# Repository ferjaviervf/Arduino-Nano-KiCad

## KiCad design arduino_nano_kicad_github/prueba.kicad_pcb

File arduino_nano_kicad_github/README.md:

# Placa basada en ATmega328 (KiCad)

Proyecto de diseño electrónico en KiCad, con esquema y circuito impreso de una placa basada en el microcontrolador **ATmega328-M**.

## Archivos

- `prueba.kicad_pro` — configuración del proyecto.
- `prueba.kicad_sch` — esquema electrónico.
- `prueba.kicad_pcb` — diseño de la placa PCB.

## Cómo abrirlo

1. Descarga o clona este repositorio.
2. Abre `prueba.kicad_pro` con KiCad.
3. Usa el editor de esquemas o PCB para revisar y modificar el diseño.

> **Estado:** Proyecto de diseño. No se han verificado aquí la compatibilidad total con Arduino Nano, las reglas eléctricas (ERC), las reglas de diseño (DRC) ni el funcionamiento de una placa fabricada.

## Publicación

Esta es la primera versión de mi placa basada en Arduino Nano. Estoy aprendiendo a usar KiCad, así que es probable que tenga algunos errores. Agradecería mucho cualquier comentario o retroalimentación para mejorarla.

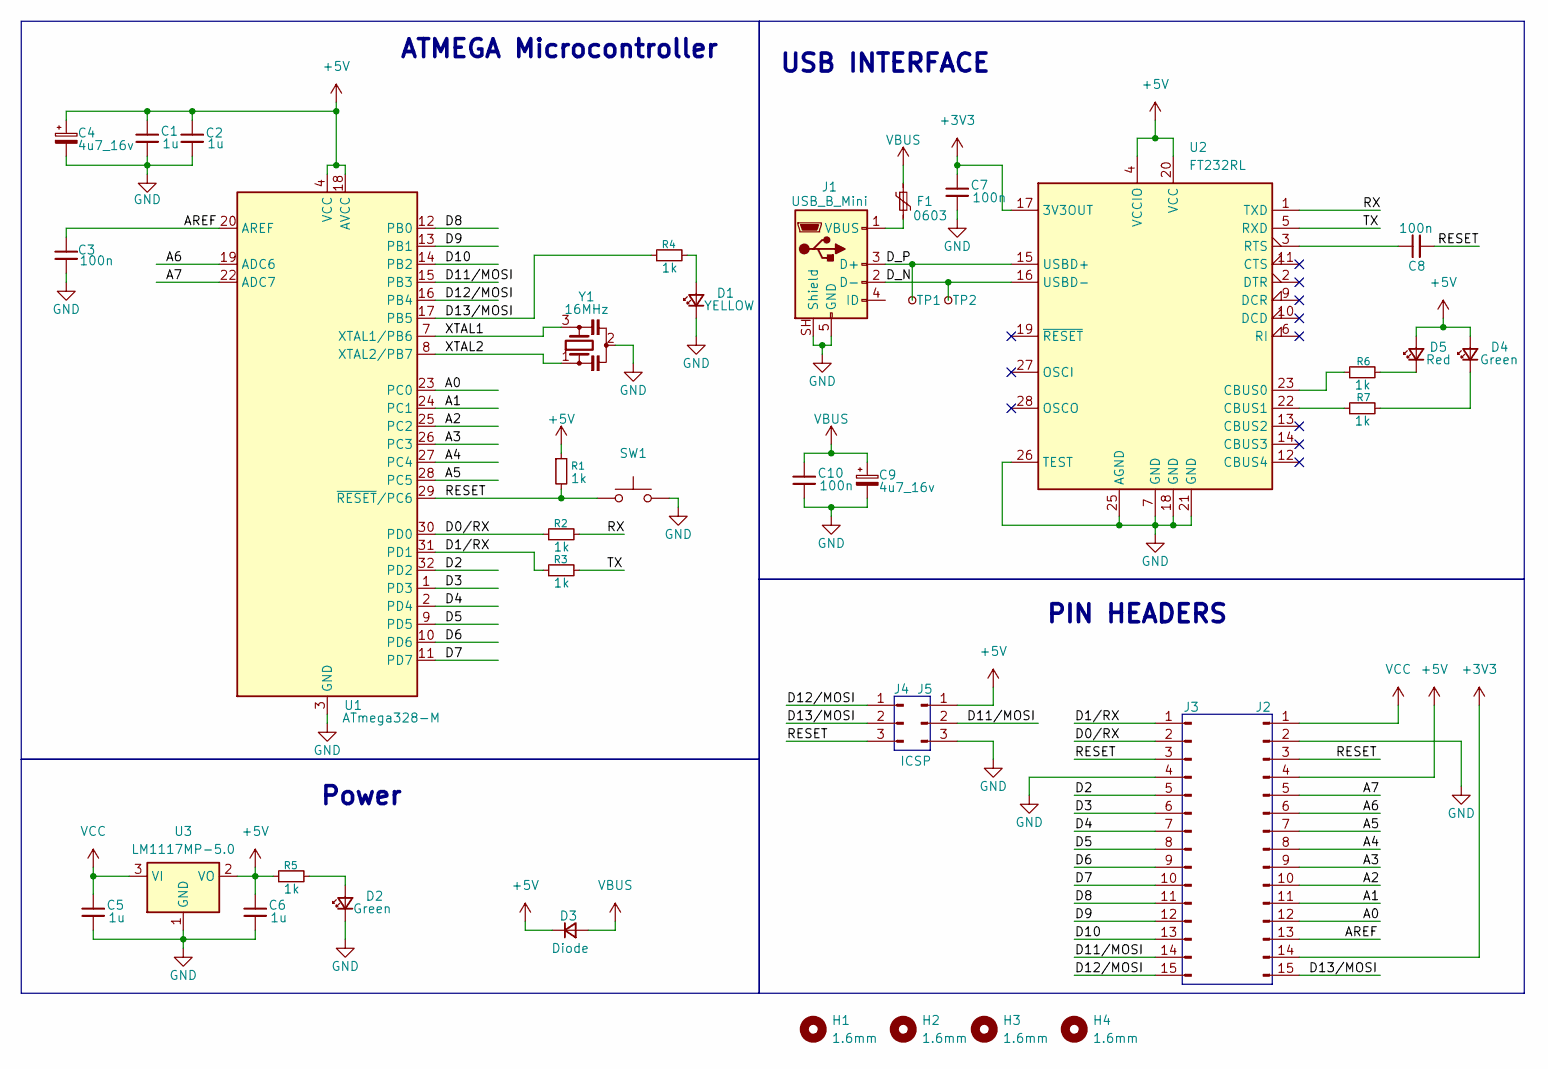
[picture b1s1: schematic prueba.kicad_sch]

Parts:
C1, C2, C5, C6: 1u; C_0603_1608Metric
C3, C7, C8, C10: 100n; C_0603_1608Metric
C4, C9: 4u7_16v; CP_EIA-3216-10_Kemet-I
D1: YELLOW; LED_0805_2012Metric
D2, D4: Green; LED_0805_2012Metric
D3: Diode; D_MicroSMP_LargeCathode
D5: Red; LED_0805_2012Metric
F1: 0603; D_0603_1608Metric
H1, H2, H3, H4: 1.6mm; MountingHole_2mm
J1: USB_B_Mini; USB_Mini-B_Lumberg_2486_01_Horizontal
J2, J3: Conn_01x15_Pin; PinHeader_1x15_P2.54mm_Vertical
J4, J5: ICSP; PinHeader_1x03_P2.54mm_Vertical
R1, R2, R3, R4, R5, R6, R7: 1k; D_0603_1608Metric
SW1: SW_Push; Panasonic_EVQPUK_EVQPUB
TP1, TP2: TestPoint_Pad_D1.0mm
U1: ATmega328-M; QFN-32-1EP_5x5mm_P0.5mm_EP3.3x3.3mm
U2: FT232RL; SSOP-28_5.3x10.2mm_P0.65mm
U3: LM1117MP-5.0; SOT-223-3_TabPin2
Y1: 16MHz; Resonator_SMD_Murata_CSTxExxV-3Pin_3.0x1.1mm

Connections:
+3V3: C7.1, J2.14, U2.17 (3V3OUT)
+5V: C1.1, C2.1, C4.1, C6.1, D3.1 (K), D4.2 (A), D5.2 (A), J2.4, J5.1, R1.1, R5.1, U1.4 (VCC), U1.6 (VCC), U1.18 (AVCC), U2.4 (VCCIO), U2.20 (VCC), U3.2 (VO)
/A0: J2.12, U1.23 (PC0)
/A1: J2.11, U1.24 (PC1)
/A2: J2.10, U1.25 (PC2)
/A3: J2.9, U1.26 (PC3)
/A4: J2.8, U1.27 (PC4)
/A5: J2.7, U1.28 (PC5)
/A6: J2.6, U1.19 (ADC6)
/A7: J2.5, U1.22 (ADC7)
/AREF: C3.1, J2.13, U1.20 (AREF)
/D0/RX: J3.2, R2.1, U1.30 (PD0)
/D1/RX: J3.1, R3.1, U1.31 (PD1)
/D2: J3.5, U1.32 (PD2)
/D3: J3.6, U1.1 (PD3)
/D4: J3.7, U1.2 (PD4)
/D5: J3.8, U1.9 (PD5)
/D6: J3.9, U1.10 (PD6)
/D7: J3.10, U1.11 (PD7)
/D8: J3.11, U1.12 (PB0)
/D9: J3.12, U1.13 (PB1)
/D10: J3.13, U1.14 (PB2)
/D11/MOSI: J3.14, J5.2, U1.15 (PB3)
/D12/MOSI: J3.15, J4.1, U1.16 (PB4)
/D13/MOSI: J2.15, J4.2, R4.1, U1.17 (PB5)
/D_N: J1.2 (D-), TP2.1 (1_1), U2.16 (USBD-)
/D_P: J1.3 (D+), TP1.1 (1_1), U2.15 (USBD+)
/RESET: C8.1, J2.3, J3.3, J4.3, R1.2, SW1.1, U1.29 (~RESET/PC6)
/RX: R2.2, U2.1 (TXD)
/TX: R3.2, U2.5 (RXD)
/XTAL1: U1.7 (XTAL1/PB6), Y1.3
/XTAL2: U1.8 (XTAL2/PB7), Y1.1
GND: C1.2, C2.2, C3.2, C4.2, C5.2, C6.2, C7.2, C9.2, C10.2, D1.1 (K), D2.1 (K), J1.5 (GND), J1.SH (Shield), J2.2, J3.4, J5.3, SW1.2, U1.3 (GND), U1.5 (GND), U1.21 (GND), U1.33 (GND), U2.7 (GND), U2.18 (GND), U2.21 (GND), U2.25 (AGND), U2.26 (TEST), U3.1 (GND), Y1.2
unnamed: D1.2 (A), R4.2
unnamed: D2.2 (A), R5.2
unnamed: D4.1 (K), R7.2
unnamed: D5.1 (K), R6.2
unnamed: F1.2, J1.1 (VBUS)
unnamed: R6.1, U2.23 (CBUS0)
unnamed: R7.1, U2.22 (CBUS1)
unnamed: C8.2, U2.3 (RTS)
VBUS: C9.1, C10.1, D3.2 (A), F1.1
VCC: C5.1, J2.1, U3.3 (VI)

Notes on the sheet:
Power
USB INTERFACE
ATMEGA Microcontroller
PIN HEADERS

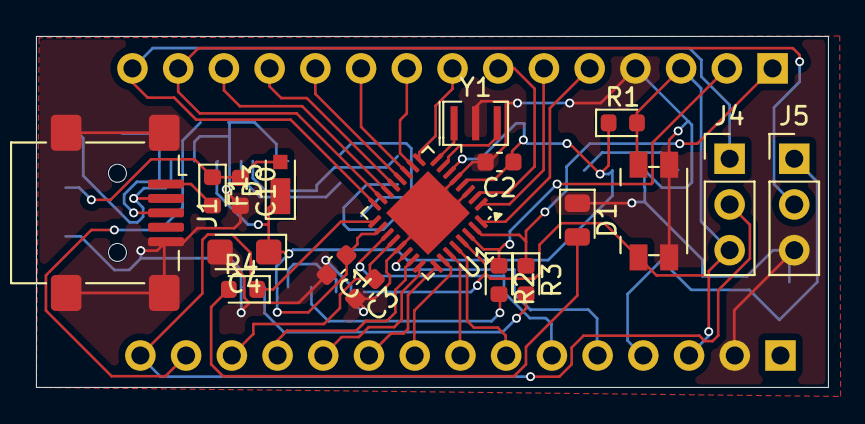
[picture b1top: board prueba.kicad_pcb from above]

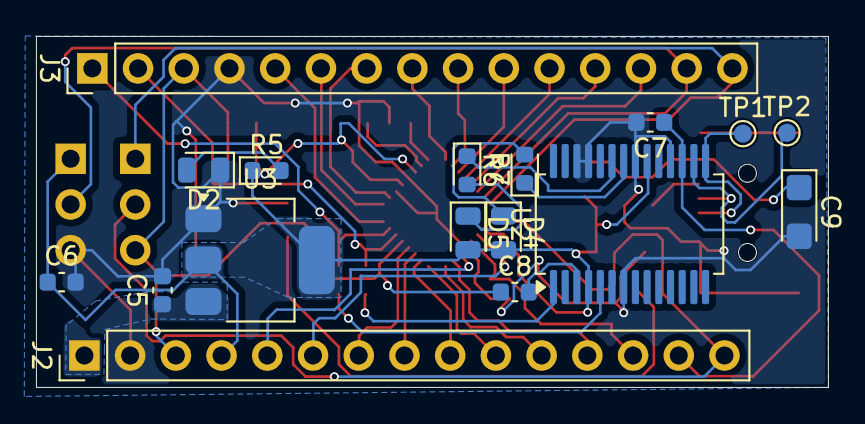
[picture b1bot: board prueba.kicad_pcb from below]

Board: 2 copper layers, 44.0 x 19.5 mm, 39 parts (17 on the bottom side), 43 nets.
